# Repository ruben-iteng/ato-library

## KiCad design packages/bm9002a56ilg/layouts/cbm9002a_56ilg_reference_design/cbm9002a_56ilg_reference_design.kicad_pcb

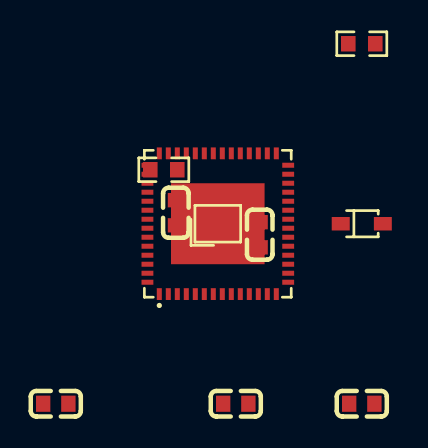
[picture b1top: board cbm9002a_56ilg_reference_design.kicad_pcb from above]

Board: 2 copper layers, 10 parts (0 on the bottom side), 8 nets.

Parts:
C1, C2, C3, C4: 100nF ±10% 50V X7R; C0603-bd72f6
C5: 1µF ±5% 16V X7R; C0603-bd72f6
D1: SOD-323_L1.8-W1.3-LS2.5-RD-b55baa
R1, R2: 10kΩ ±1% 100mW; R0603-ebcab9
U1: QFN-56_L8.0-W8.0-P0.50-BL-EP-2e306a
XTAL1: CRYSTAL-SMD_4P-L2.0-W1.6-BL-A-5567c7

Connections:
anode: C5.1, D1.2, R2.1, U1.42
gnd: C2.2, C3.2, C4.2, C5.2, U1.12, U1.14, U1.26, U1.28, U1.41, U1.53, U1.56, U1.57, XTAL1.2, XTAL1.4
gnd-1: C1.2, U1.6, U1.10
hv: C2.1, D1.1, R2.2, U1.11, U1.17, U1.27, U1.32, U1.43, U1.55
hv-1: C1.1, U1.3, U1.7
net: C3.1, R1.1, XTAL1.1
xtalin: C4.1, U1.5, XTAL1.3
xtalout: R1.2, U1.4
